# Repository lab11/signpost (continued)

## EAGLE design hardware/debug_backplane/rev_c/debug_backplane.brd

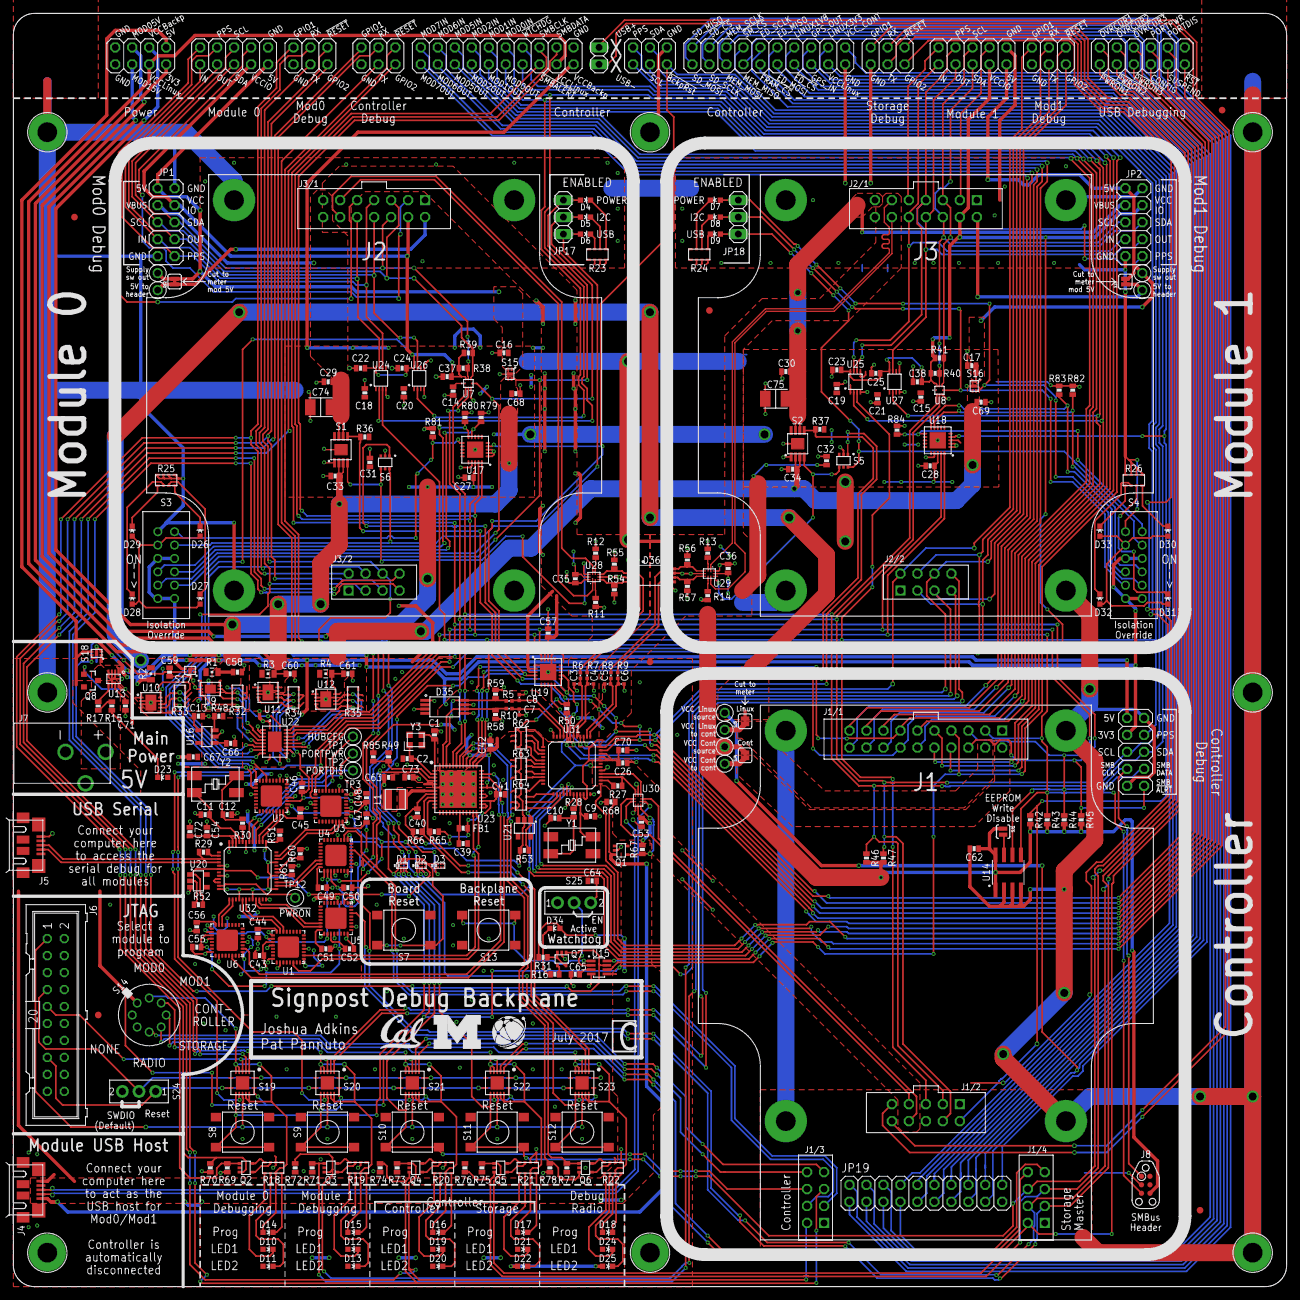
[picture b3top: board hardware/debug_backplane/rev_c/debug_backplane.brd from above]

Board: 2 copper layers, 190.5 x 190.5 mm, 327 parts (0 on the bottom side), 293 nets.

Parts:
C1, C2: 8pF; 0603_CAP
C3, C4, C5, C6, C7, C8: 22pF; 0402_CAP
C9, C10, C11, C12: 22pF; 0603_CAP
C13: 0.01uF; 0603_CAP
C14, C15, C16, C17, C18, C19, C20, C21, C22, C23, C24, C25, C26, C27, C28, C29, C30, C31, C32, C33, C34, C35, C36, C37, C38, C39, C40, C41, C42, C43, C44, C45, C46, C47, C48, C49, C50, C51, C52, C53, C54, C55, C56, C57, C58, C59, C60, C61, C62, C63: 0.1uF; 0603_CAP
C64: 0.47uF; 0603_CAP
C65: 0.82uF; 0603_CAP
C66, C67: 2.2uF; 0603_CAP
C68, C69, C70, C71, C72: 4.7uF; 0603_CAP
C73: 6.8uF; 0603_CAP
C74, C75: 150uF; 1210_CAP
D1, D2, D3: DIODE_SCHOTTKY_ARRAY-4HMD8; HMD8
D4, D5, D6, D7, D8, D9, D10, D11, D12, D13, D14, D15, D16, D17, D18, D19, D20, D21, D22, D23, D24, D25, D26, D27, D28, D29, D30, D31, D32, D33, D34: LED0603; LED-0603
D35, D36: SN75240-TSSOP; TSSOP-8
FB1: 1.5kR; 0603_CAP
H1, H2, H3, H4, H5, H6, H7, H8: MOUNT-PAD-ROUND#4; #4-PAD
J1: BACKPLANE_CONTROLLER_MODULE_DEBUG; BACKPLANE_MODULE_20PIN_10PIN_DEBUG
J2, J3: BACKPLANE_GENERIC_MODULE_DEBUG; BACKPLANE_MODULE_14PIN_8PIN
J4, J5: MICRO_USB_B_HIROSE_ZX62R-B-5P; USB_MICRO_B-HIROSE-ZX62R-B-5P
J6: ML20
J7: PJ-102AH
J8: TC2030-FTDI-I2C; TC2030-IDC-NL
JP1, JP2, JP4, JP5, JP11: 2X05
JP3, JP6, JP7, JP8, JP9, JP10, JP14: 2X03
JP12, JP19, JP20: 2X10
JP13: 1X02
JP15, JP21, JP22, JP23, JP24, JP25: FIDUCIAL1X2; FIDUCIAL-1X2
JP16: 2X04
JP17, JP18: 1X03
L1: 22uH; 1212
Q1, Q2, Q3, Q4, Q5, Q6, Q7: DMN32D2LDF; SOT353
Q8: MOSFET-NCHANNELSMD; SOT23-3
R1, R2, R3, R4: 0.017Ω; 0805_RES
R5, R6, R7, R8, R9, R10: 27Ω; 0402_RES-HIGH_SPEED
R11, R12, R13, R14, R15, R16, R17: 50Ω; 0603-RES
R18, R19, R20, R21, R22, R23, R24, R25, R26: 1kΩ; ARRAY-CONVEX-0603-4
R27, R28, R29, R30, R31: 1.5kΩ; 0603-RES
R32, R33, R34, R35: 1.8kΩ; ARRAY-CONVEX-0603-4
R36, R37, R38, R39, R40, R41, R42, R43, R44, R45, R46, R47, R48, R49, R50, R51, R52, R53: 10kΩ; 0603-RES
R54, R55, R56, R57, R58, R59, R60, R61: 15kΩ; 0603-RES
R62, R63, R64: 15kΩ; ARRAY-CONVEX-0603-4
R65, R66, R67, R68: 100kΩ; 0603-RES
R69, R70, R71, R72, R73, R74, R75, R76, R77, R78: 1MΩ; 0603-RES
R79, R80, R81, R82, R83, R84: 10MΩ; 0603-RES
R85: DNP; 0603-RES
S1, S2: AP2401MP; MSOP-8EP
S3, S4: MMS42
S5, S6: NC7SZ157; SC70-6
S7, S8, S9, S10, S11, S12, S13: PTS645SM43SMTR92; PTS645
S14: RM106772BCB; RM-SWITCH
S15, S16, S17, S18: SIP3240X; TDFN4
S19, S20, S21, S22, S23: SN74AHC4066-RGY; S-PVQFN-N14-3.5MM
S24, S25: TE_SSA12/SPDT
SJ1: SOLDERJUMPERNO; SJ_2S-NO
SJ2, SJ3, SJ4, SJ5: SOLDERJUMPERNC; SJ_2S
TP1, TP2, TP3, TP4, TP5, TP6, TP7, TP8, TP9, TP10, TP11, TP12: TEST_POINT_0.040IN; TESTPOINT_0.040IN
U1, U2, U3, U4, U5, U6: FT232RQ; QFN32
U7, U8: FXMA2102; UMLP-8
U9: LTC2941; DFN-6-2MMX3MM
U10, U11, U12: LTC2943; DFN-8
U13: LTC4360; SC70-8
U14: M24C01WMN; SOIC-8
U15: MAX6746; SOT-23-8
U16: MAX8887EZK33+T; SOT-23-5
U17, U18, U19: MCP23008QFN; QFN-20-4MM
U20, U21: NCP301LSN30; SOT23-5
U22: PCA9544AQFN-N20; QFN-N20
U23: SAM4LC8AA; QFN-48-7MM
U24, U25, U26, U27: SN74LVC2T45; VFSOP-8
U28, U29, U30: TS3USB30E; UQFN-10
U31, U32: TUSB2077A; LQFP-48
U$12: UMICH_SOLID_200MIL
U$15: UCB_CAL_200MIL
U$28: TERRASWARM_200MIL
Y1, Y2: ABMM
Y3: FH1600015; FHXXX

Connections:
3V3_UNMETERED: C40.1, C41.1, C42.1, C53.2, C54.2, C67.1, C72.2, D10.A, D11.A, D12.A, D13.A, D19.A, D20.A, D21.A, D22.A, D24.A, D25.A, D34.A, FB1.2, JP11.3, JP16.2, R31.2, R51.2, R52.2, R65.2, R66.2, R67.2, R85.2, S3.B1, S3.B2, S3.B3, S3.B4, S4.B1, S4.B2, S4.B3, S4.B4, S14.C, S17.3, S19.14, S20.14, S21.10, S21.14, S22.10, S22.14, S23.10, S23.14, U1.1, U6.1, U15.5, U15.8, U16.5, U20.2, U23.8, U23.27, U23.31, U23.40, U23.45, U30.9, U32.9, U32.10, U32.46, U32.47
3V3_WATCHDOGGED: R1.2, R32.A2, R32.B2, R32.C2, S17.1, U9.1
5V_UNMETERED: C43.1, C46.1, C48.1, C50.1, C52.1, C55.1, C66.1, C71.1, D23.A, JP11.1, JP16.1, Q8.2, R48.2, S18.3, U1.19, U2.19, U3.19, U4.19, U5.19, U6.19, U13.7, U16.1
5V_WATCHDOGGED: R2.2, R3.2, R4.2, R33.A2, R33.B2, R33.C2, R34.A2, R34.B2, R34.C2, R35.A2, R35.B2, R35.C2, S18.1, U10.P1, U11.P1, U12.P1
!BACKPLANE_RESET: D3.1A, J1.22, JP14.2, R42.1, U17.4, U18.4, U19.4
!POWER_ON_RESET: D2.4A, R52.1, U20.1, U32.6
!SMBALERT: J1.6, JP11.10, JP12.6, R45.1, U22.17
!WATCHDOG: J1.7, JP12.7, U15.6
CONT0_!RESET: D1.3A, J1.105, JP9.1, S10.3, S10.4, S21.9
CONT0_DBG_GPIO1: J1.101, JP9.5, Q4.G1, R73.2
CONT0_DBG_GPIO2: J1.104, JP9.2, Q4.G2, R74.2
CONT0_DBG_RX: J1.103, JP9.3, U4.30
CONT0_DBG_TX: J1.102, JP9.4, U4.2
CONT0_SWDCLK: J1.106, S21.3
CONT0_SWDIO: J1.107, S21.2
CONT0_VCCIO: C49.1, U4.16
CONT1_!RESET: D1.4A, J1.205, JP10.1, S11.3, S11.4, S22.9
CONT1_DBG_GPIO1: J1.201, JP10.5, Q5.G1, R75.2
CONT1_DBG_GPIO2: J1.204, JP10.2, Q5.G2, R76.2
CONT1_DBG_RX: J1.203, JP10.3, U5.30
CONT1_DBG_TX: J1.202, JP10.4, U5.2
CONT1_SWDCLK: J1.206, S22.3
CONT1_SWDIO: J1.207, S22.2
CONT1_VCCIO: C51.1, U5.16
CONTROLLER_BUCK/LDO_N: R49.2, R85.1, U23.3
CONT_DBG_PIN1: JP19.1, JP20.1
CONT_DBG_PIN2: JP19.2, JP20.2
CONT_DBG_PIN3: JP19.3, JP20.3
CONT_DBG_PIN4: JP19.4, JP20.4
CONT_DBG_PIN5: JP19.5, JP20.5
CONT_DBG_PIN6: JP19.6, JP20.6
CONT_DBG_PIN7: JP19.7, JP20.7
CONT_DBG_PIN8: JP19.8, JP20.8
CONT_DBG_PIN9: JP19.9, JP20.9
CONT_DBG_PIN10: JP19.10, JP20.10
CONT_DBG_PIN11: JP19.11, JP20.11
CONT_DBG_PIN12: JP19.12, JP20.12
CONT_DBG_PIN13: JP19.13, JP20.13
CONT_DBG_PIN14: JP19.14, JP20.14
CONT_DBG_PIN15: JP19.15, JP20.15
CONT_DBG_PIN16: JP19.16, JP20.16
CONT_DBG_PIN18: JP19.18, JP20.18
CONT_DBG_PIN20: JP19.20, JP20.20
CONT_MOD0_IN: J1.9, JP12.9, U24.2
CONT_MOD0_OUT: J1.10, JP12.10, U26.2
CONT_MOD1_IN: J1.11, JP12.11, U25.2
CONT_MOD1_OUT: J1.12, JP12.12, U27.2
CONT_MOD2_IN: J1.13, JP12.13, U23.39
CONT_MOD2_OUT: J1.14, JP12.14, U23.38
CONT_MOD5_IN: J1.15, JP12.15
CONT_MOD5_OUT: J1.16, JP12.16
CONT_MOD6_IN: J1.17, JP12.17
CONT_MOD6_OUT: J1.18, JP12.18
CONT_MOD7_IN: J1.19, JP12.19
CONT_MOD7_OUT: J1.20, JP12.20
CONT_USB+: J1.27, U30.6
CONT_USB-: J1.28, U30.2
DBG_USB_!PWRON: TP12.TESTPOINT, U32.11
DBG_USB_DM0: J5.2, U32.4
DBG_USB_DM1: U6.15, U32.13
DBG_USB_DM2: U1.15, U32.17
DBG_USB_DM3: U5.15, U32.21
DBG_USB_DM4: U4.15, U32.26
DBG_USB_DM5: R61.1, U32.30
DBG_USB_DM6: U3.15, U32.34
DBG_USB_DM7: U2.15, U32.38
DBG_USB_DP0: J5.3, R29.1, U32.3
DBG_USB_DP1: U6.14, U32.14
DBG_USB_DP2: U1.14, U32.18
DBG_USB_DP3: U5.14, U32.22
DBG_USB_DP4: U4.14, U32.27
DBG_USB_DP5: R60.1, U32.31
DBG_USB_DP6: U3.14, U32.35
DBG_USB_DP7: U2.14, U32.39
DBG_USB_HUBCFG: TP1.TESTPOINT, U32.40
DBG_USB_PORTDIS: TP3.TESTPOINT, U32.42
DBG_USB_PORTPWR: TP2.TESTPOINT, U32.41
DBG_USB_XTAL1: C11.2, U32.45, Y2.3
DBG_USB_XTAL2: R30.2, U32.44
DEBUG_HUB_!OVRCURX: R51.1, U32.12, U32.16, U32.20, U32.25, U32.29, U32.33, U32.37
FAKE_RADIO_XIN: C1.1, U23.1, Y3.3
FAKE_RADIO_XOUT: C2.1, U23.2, Y3.1
FTDI_!RESET: D2.3A, U1.18, U2.18, U3.18, U4.18, U5.18, U6.18
GND: C1.2, C2.2, C3.2, C4.2, C5.2, C6.2, C7.2, C8.2, C9.1, C10.1, C11.1, C12.1, C13.2, C14.2, C15.2, C16.2, C17.2, C18.2, C19.2, C20.2, C21.2, C22.2, C23.2, C24.2, C25.2, C26.1, C27.2, C28.2, C29.2, C30.2, C31.2, C32.2, C33.2, C34.2, C35.1, C36.1, C37.2, C38.2, C39.2, C40.2, C41.2, C42.2, C43.2, C44.2, C45.2, C46.2, C47.2, C48.2, C49.2, C50.2, C51.2, C52.2, C53.1, C54.1, C55.2, C56.2, C57.2, C58.2, C59.2, C60.2, C61.2, C62.2, C63.2, C64.2, C65.2, C66.2, C67.2, C68.2, C69.2, C70.1, C71.2, C72.1, C73.2, C74.2, C75.2, D35.1, D35.3, D35.5, D35.7, D36.1, D36.3, D36.5, D36.7, H1.B#4, H2.B#4, H3.B#4, H4.B#4, H5.B#4, H6.B#4, H7.B#4, H8.B#4, J1.1, J1.21, J1.100, J1.200, J1.MNT1, J1.MNT2, J1.MNT3, J1.MNT4, J2.1, J2.14, J2.15, J2.MNT1, J2.MNT2, J2.MNT3, J2.MNT4, J3.1, J3.14, J3.15, J3.MNT1, J3.MNT2, J3.MNT3, J3.MNT4, J4.5, J5.5, J6.4, J6.6, J6.8, J6.10, J6.12, J6.14, J6.16, J6.18, J6.20, J7.2, J8.3, JP1.2, JP1.9, JP2.2, JP2.9, JP3.6, JP4.1, JP5.1, JP6.6, JP9.6, JP10.6, JP11.2, JP11.9, JP12.1, JP14.1, JP16.7, JP16.8, JP19.19, JP20.19, Q1.S, Q2.S, Q3.S, Q4.S, Q5.S, Q6.S, Q7.S, R11.2, R12.2, R13.2, R14.2, R18.C1, R18.D1, R19.C1, R19.D1, R20.C1, R20.D1, R21.C1, R21.D1, R22.C1, R22.D1, R23.A1, R23.B1, R23.C1, R24.A1, R24.B1, R24.C1, R25.A2, R25.B2, R25.C2, R25.D2, R26.A2, R26.B2, R26.C2, R26.D2, R49.1, R54.1, R55.1, R56.1, R57.1, R58.1, R59.1, R60.2, R61.2, R62.B2, R62.C2, R63.A2, R63.B2, R63.D2, R64.A2, R64.C2, R64.D2, R68.1, R69.1, R70.1, R71.1, R72.1, R73.1, R74.1, R75.1, R76.1, R77.1, R78.1, R79.1, R80.1, R81.1, R82.1, R83.1, R84.1, S1.1, S1.PAD, S2.1, S2.PAD, S3.A1, S4.A1, S5.2, S6.2, S7.3, S7.4, S8.1, S8.2, S9.1, S9.2, S10.1, S10.2, S11.1, S11.2, S12.1, S12.2, S13.1, S13.2, S15.2, S15.PAD, S16.2, S16.PAD, S17.2, S17.PAD, S18.2, S18.PAD, S19.7, S20.7, S21.7, S22.7, S23.7, S25.1, U1.4, U1.17, U1.20, U1.24, U1.26, U2.4, U2.17, U2.20, U2.24, U2.26, U3.4, U3.17, U3.20, U3.24, U3.26, U4.4, U4.17, U4.20, U4.24, U4.26, U5.4, U5.17, U5.20, U5.24, U5.26, U6.4, U6.17, U6.20, U6.24, U6.26, U7.4, U8.4, U9.2, U10.P2, U10.P3, U10.P7, U10.P$1, U11.P2, U11.P3, U11.P7, U11.P$1, U12.P2, U12.P3, U12.P7, U12.P$1, U13.2, U13.3, U13.4, U13.6, U14.2, U14.3, U14.4, U15.4, U16.2, U17.1, U17.2, U17.3, U17.17, U17.GND, U18.1, U18.2, U18.17, U18.GND, U19.1, U19.17, U19.GND, U20.3, U21.3, U22.1, U22.2, U22.3, U22.10, U23.6, U23.17, U23.30, U23.48, U23.THERMAL, U24.4, U25.4, U26.4, U26.5, U27.4, U27.5, U28.4, U28.10, U29.4, U29.10, U30.4, U30.8, U31.5, U31.24, U31.43, U31.48, U32.5, U32.8, U32.24, U32.43, U32.48, Y3.2, Y3.4
HUB_!OVRCUR1: JP8.2, R37.1, S2.5, U31.12
HUB_!OVRCUR2: JP8.4, R36.1, S1.5, U31.16
HUB_!OVRCUR3: JP8.6, R50.1, U31.20
HUB_!OVRCUR4: R62.A1, U31.25
HUB_!OVRCUR5: R62.D1, U31.29
HUB_!OVRCUR6: R63.C1, U31.33
HUB_!OVRCUR7: R64.B1, U31.37
HUB_!PWRON1: JP8.1, S5.1, U19.10, U31.11
HUB_!PWRON2: JP8.3, S6.1, U19.11, U31.15
HUB_!PWRON3: JP8.5, U19.12, U31.19
HUB_CFG: JP7.1, U31.40
HUB_DM1: C6.1, R9.2, U31.13
HUB_DM2: C4.1, R7.2, U31.17
HUB_DM3: C8.1, R5.2, U31.21
HUB_DM4: R62.B1, U31.26
HUB_DM5: R63.A1, U31.30
HUB_DM6: R63.D1, U31.34
HUB_DM7: R64.C1, U31.38
HUB_DP1: C5.1, R8.2, U31.14
HUB_DP2: C3.1, R6.2, U31.18
HUB_DP3: C7.1, R10.2, U31.22
HUB_DP4: R62.C1, U31.27
HUB_DP5: R63.B1, U31.31
HUB_DP6: R64.A1, U31.35
HUB_DP7: R64.D1, U31.39
HUB_PORTDIS: JP7.4, U31.42
HUB_PORTPWR: JP7.2, U31.41
JTAG_!RESET: J6.15, S19.8, S20.8, S21.8, S22.8, S23.8, S24.1
JTAG_SWDCLK: J6.9, S19.4, S20.4, S21.4, S22.4, S23.4
JTAG_SWDIO: J6.7, S19.1, S20.1, S21.1, S22.1, S23.1, S24.IN
JTAG_VTREF: J6.1, S19.11, S20.11, S21.11, S22.11, S23.11
MASTER_!RESET: D1.1K, D1.2K, D1.3K, D1.4K, D2.1K, D2.2K, D2.3K, D2.4K, D3.1K, S7.1, S7.2
MOD0_5V: C16.1, JP1.1, JP4.2, S15.1, SJ2.2, TP5.TESTPOINT
MOD0_5V_HEADER: J2.2, SJ2.1, TP4.TESTPOINT
MOD0_5V_METERED: C33.1, C60.1, C68.1, JP16.5, R3.1, S1.2, S1.3, S15.3, U11.P8
MOD0_D+_HUB-SW: D36.4, R6.1, R54.2, U28.3
MOD0_D-_HUB-SW: D36.2, R7.1, R55.2, U28.5
MOD0_DBG_!RESET: D1.1A, J2.20, JP3.1, S8.3, S8.4, S19.9
MOD0_DBG_GPIO1: J2.16, JP3.5, Q2.G1, R69.2
MOD0_DBG_GPIO2: J2.19, JP3.2, Q2.G2, R70.2
MOD0_DBG_RX: J2.18, JP3.3, U2.30
MOD0_DBG_SWDCLK: J2.21, S19.3
MOD0_DBG_SWDIO: J2.22, S19.2
MOD0_DBG_TX: J2.17, JP3.4, U2.2
MOD0_IN: J2.10, JP1.7, JP4.10, U24.7
MOD0_ISO_I2C: D5.A, JP17.2, S3.COM3, U7.5
MOD0_ISO_OVERRIDE: D26.A, D27.A, D28.A, D29.A, S3.COM1
MOD0_ISO_P0: R79.2, S3.A4, U17.9
MOD0_ISO_P1: R80.2, S3.A3, U17.10
MOD0_ISO_P2: R81.2, S3.A2, U17.11
MOD0_ISO_POWER: D4.A, JP17.3, S3.COM4, S15.4
MOD0_ISO_USB: D6.A, JP17.1, S3.COM2, S6.6
MOD0_OUT: J2.8, JP1.8, JP4.8, U26.7
MOD0_PPS: J2.7, JP1.10, JP4.7, U24.6
MOD0_SCL: J2.5, JP1.5, JP4.5, R39.2, U7.6
MOD0_SDA: J2.6, JP1.6, JP4.6, R38.2, U7.7
MOD0_USB+: J2.11, U28.1
MOD0_USB-: J2.12, U28.7
MOD0_USB_!EN: S1.4, S6.4, U28.8
MOD0_USB_VBUS: C29.1, C74.1, J2.13, JP1.3, S1.6, S1.7
MOD0_VCCIO: C22.1, C24.1, C37.1, J2.4, JP1.4, JP4.4, R38.1, R39.1, S19.10, U2.1, U7.8, U24.8, U26.8
MOD1_5V: C17.1, JP2.1, JP5.2, S16.1, SJ3.2, TP7.TESTPOINT
MOD1_5V_HEADER: J3.2, SJ3.1, TP6.TESTPOINT
MOD1_5V_METERED: C34.1, C61.1, C69.1, JP16.6, R4.1, S2.2, S2.3, S16.3, U12.P8
MOD1_D+_HUB-SW: D36.8, R8.1, R56.2, U29.3
MOD1_D-_HUB-SW: D36.6, R9.1, R57.2, U29.5
MOD1_DBG_!RESET: D1.2A, J3.20, JP6.1, S9.3, S9.4, S20.9
MOD1_DBG_GPIO1: J3.16, JP6.5, Q3.G1, R71.2
MOD1_DBG_GPIO2: J3.19, JP6.2, Q3.G2, R72.2
MOD1_DBG_RX: J3.18, JP6.3, U3.30
MOD1_DBG_SWDCLK: J3.21, S20.3
MOD1_DBG_SWDIO: J3.22, S20.2
MOD1_DBG_TX: J3.17, JP6.4, U3.2
MOD1_IN: J3.10, JP2.7, JP5.10, U25.7
MOD1_ISO_I2C: D8.A, JP18.2, S4.COM3, U8.5
MOD1_ISO_OVERRIDE: D30.A, D31.A, D32.A, D33.A, S4.COM1
MOD1_ISO_P0: R82.2, S4.A4, U18.9
MOD1_ISO_P1: R83.2, S4.A3, U18.10
MOD1_ISO_P2: R84.2, S4.A2, U18.11
MOD1_ISO_POWER: D7.A, JP18.3, S4.COM4, S16.4
MOD1_ISO_USB: D9.A, JP18.1, S4.COM2, S5.6
MOD1_OUT: J3.8, JP2.8, JP5.8, U27.7
MOD1_PPS: J3.7, JP2.10, JP5.7, U25.6
MOD1_SCL: J3.5, JP2.5, JP5.5, R41.2, U8.6
MOD1_SDA: J3.6, JP2.6, JP5.6, R40.2, U8.7
MOD1_USB+: J3.11, U29.1
MOD1_USB-: J3.12, U29.7
MOD1_USB_!EN: S2.4, S5.4, U29.8
MOD1_USB_VBUS: C30.1, C75.1, J3.13, JP2.3, S2.6, S2.7
MOD1_VCCIO: C23.1, C25.1, C38.1, J3.4, JP2.4, JP5.4, R40.1, R41.1, S20.10, U3.1, U8.8, U25.8, U27.8
MOD2_DBG_GPIO1: Q6.G1, R77.2, U23.41
MOD2_DBG_GPIO2: Q6.G2, R78.2, U23.42
MOD2_USB+: D35.6, R10.1, R58.2, U23.47
MOD2_USB-: D35.8, R5.1, R59.2, U23.46
MOD_SCL: J1.24, JP11.5, JP14.4, R47.1, U7.3, U8.3, U23.44
MOD_SDA: J1.23, JP11.6, JP14.3, R46.1, U7.2, U8.2, U23.43
MOD_USB_OVERRIDE_5V: J4.1, Q1.G2, R68.2
MOD_USB_OVERRIDE_DM: J4.2, U30.1
MOD_USB_OVERRIDE_DP: J4.3, U30.7
unnamed: D4.C, R23.A2
unnamed: D5.C, R23.B2
unnamed: D6.C, R23.C2
unnamed: R48.1, U16.3
unnamed: D10.C, R18.A2
unnamed: D11.C, R18.B2
unnamed: C13.1, U16.4
unnamed: Q2.D1, R18.A1
unnamed: Q2.D2, R18.B1
unnamed: D7.C, R24.C2
unnamed: D9.C, R24.A2
unnamed: R27.2, U31.2
unnamed: D8.C, R24.B2
unnamed: C10.2, R28.1, Y1.1
unnamed: D12.C, R19.A2
unnamed: D13.C, R19.B2
unnamed: R11.1, U28.2
unnamed: Q3.D1, R19.A1
unnamed: Q3.D2, R19.B1
unnamed: Q4.D1, R20.A1
unnamed: C56.1, U6.16
unnamed: Q4.D2, R20.B1
unnamed: D21.C, R21.A2
unnamed: D22.C, R21.B2
unnamed: R14.1, U29.6
unnamed: R13.1, U29.2
unnamed: D14.C, R18.D2
unnamed: Q5.D1, R21.A1
unnamed: Q5.D2, R21.B1
unnamed: R12.1, U28.6
unnamed: D15.C, R19.D2
unnamed: Q1.D2, R67.1, U30.10
unnamed: C45.1, U2.16
unnamed: D16.C, R20.D2
unnamed: D17.C, R21.D2
unnamed: C39.1, FB1.1, U23.19
unnamed: U23.28, U23.29
unnamed: U23.25, U23.26
unnamed: D18.C, R22.D2
unnamed: R32.B1, U9.4, U22.5
unnamed: SJ1.2, U14.7
unnamed: D24.C, R22.A2
unnamed: R32.A1, U9.3, U22.6
unnamed: D25.C, R22.B2
unnamed: C44.1, U1.16
unnamed: C47.1, U3.16
unnamed: R34.B1, U11.P5, U22.12
unnamed: R34.A1, U11.P4, U22.13
unnamed: R34.C1, U11.P6, U22.11
unnamed: R35.B1, U12.P5, U22.15
unnamed: R35.A1, U12.P4, U22.16
unnamed: R35.C1, U12.P6, U22.14
unnamed: Q6.D1, R22.A1
unnamed: Q6.D2, R22.B1
unnamed: D29.C, R25.D1
unnamed: D28.C, R25.C1
unnamed: D27.C, R25.B1
unnamed: D26.C, R25.A1
unnamed: C65.1, U15.3
unnamed: D30.C, R26.A1
unnamed: R32.C1, U9.5, U22.4
unnamed: R33.B1, U10.P5, U22.8
unnamed: D19.C, R20.A2
unnamed: R33.A1, U10.P4, U22.9
unnamed: R33.C1, U10.P6, U22.7
unnamed: D20.C, R20.B2
unnamed: C9.2, U31.45, Y1.3
unnamed: R28.2, U31.44
unnamed: D31.C, R26.B1
unnamed: D32.C, R26.C1
unnamed: D33.C, R26.D1
unnamed: Q7.D1, Q7.G2, R31.1
unnamed: S13.3, S13.4, U15.1
unnamed: D34.C, R16.2
unnamed: Q7.D2, R16.1
unnamed: R17.1, U13.5
unnamed: R15.1, R17.2
unnamed: D23.C, R15.2
unnamed: R29.2, U32.2
unnamed: C12.2, R30.1, Y2.1
OVERVOLT_PROT_CTL: Q8.1, U13.8
PPS: J1.25, JP11.4, JP14.5, U23.37, U24.3, U25.3
PROG0_EN: D14.A, R18.C2, S14.1, S19.5, S19.6, S19.12, S19.13
PROG1_EN: D15.A, R19.C2, S14.2, S20.5, S20.6, S20.12, S20.13
PROG2_EN: D16.A, R20.C2, S14.3, S21.5, S21.6, S21.12, S21.13
PROG3_EN: D17.A, R21.C2, S14.4, S22.5, S22.6, S22.12, S22.13
PROG4_EN: D18.A, R22.C2, S14.5, S23.5, S23.6, S23.12, S23.13
RADIO_!RESET: D2.1A, S12.3, S12.4, S23.9, U23.4
RADIO_DEBUG_RX: U6.30, U23.34
RADIO_DEBUG_TX: U6.2, U23.35
RADIO_SWDCLK: R66.1, S23.3, U23.9
RADIO_SWDIO: R65.1, S23.2, U23.10
RADIO_UPLINK_RX: U1.30, U23.23
RADIO_UPLINK_TX: U1.2, U23.24
RADIO_VDDCORE: C63.1, C73.1, L1.P$2, U23.5
RADIO_VDDOUT: L1.P$1, U23.7
SMBCLK: J1.5, J8.1, JP11.7, JP12.5, R44.1, U14.6, U17.19, U18.19, U19.19, U22.18
SMBDATA: J1.3, J8.5, JP11.8, JP12.3, R43.1, U14.5, U17.20, U18.20, U19.20, U22.19
USB+: R27.1, U30.5, U31.3
USB-: U30.3, U31.4
USB_!RESET: D2.2A, JP7.5, R53.1, U19.9, U21.1, U31.6
USB_SUSPEND_STATUS: JP7.3, U31.1
VCC_BACKPLANE: C14.1, C15.1, C18.1, C19.1, C20.1, C21.1, C26.2, C27.1, C28.1, C31.1, C32.1, C35.2, C36.2, C57.1, C58.1, C62.1, C70.2, J8.6, JP12.2, JP16.3, R1.1, R36.2, R37.2, R42.2, R43.2, R44.2, R45.2, R46.2, R47.2, R50.2, R53.2, R62.A2, R62.D2, R63.C2, R64.B2, S5.3, S5.5, S6.3, S6.5, SJ1.1, SJ4.2, TP9.TESTPOINT, U4.1, U5.1, U7.1, U8.1, U9.6, U14.1, U14.8, U17.18, U18.3, U18.18, U19.2, U19.3, U19.18, U21.2, U22.20, U24.1, U24.5, U25.1, U25.5, U26.1, U27.1, U28.9, U29.9, U31.8, U31.9, U31.10, U31.46, U31.47
VCC_BARRELJACK: J7.1, Q8.3, U13.1
VCC_CONTROLLER_HEADER: J1.2, SJ4.1, TP8.TESTPOINT
VCC_LINUX: C59.1, JP12.4, JP16.4, JP19.17, JP20.17, R2.1, SJ5.2, TP11.TESTPOINT, U10.P8
VCC_LINUX_HEADER: J1.4, SJ5.1, TP10.TESTPOINT
WATCHDOG_!RESET: Q7.G1, S17.4, S18.4, U15.7
WDT_CTRL: S25.IN, U15.2
WDT_ON: C64.1, S25.2

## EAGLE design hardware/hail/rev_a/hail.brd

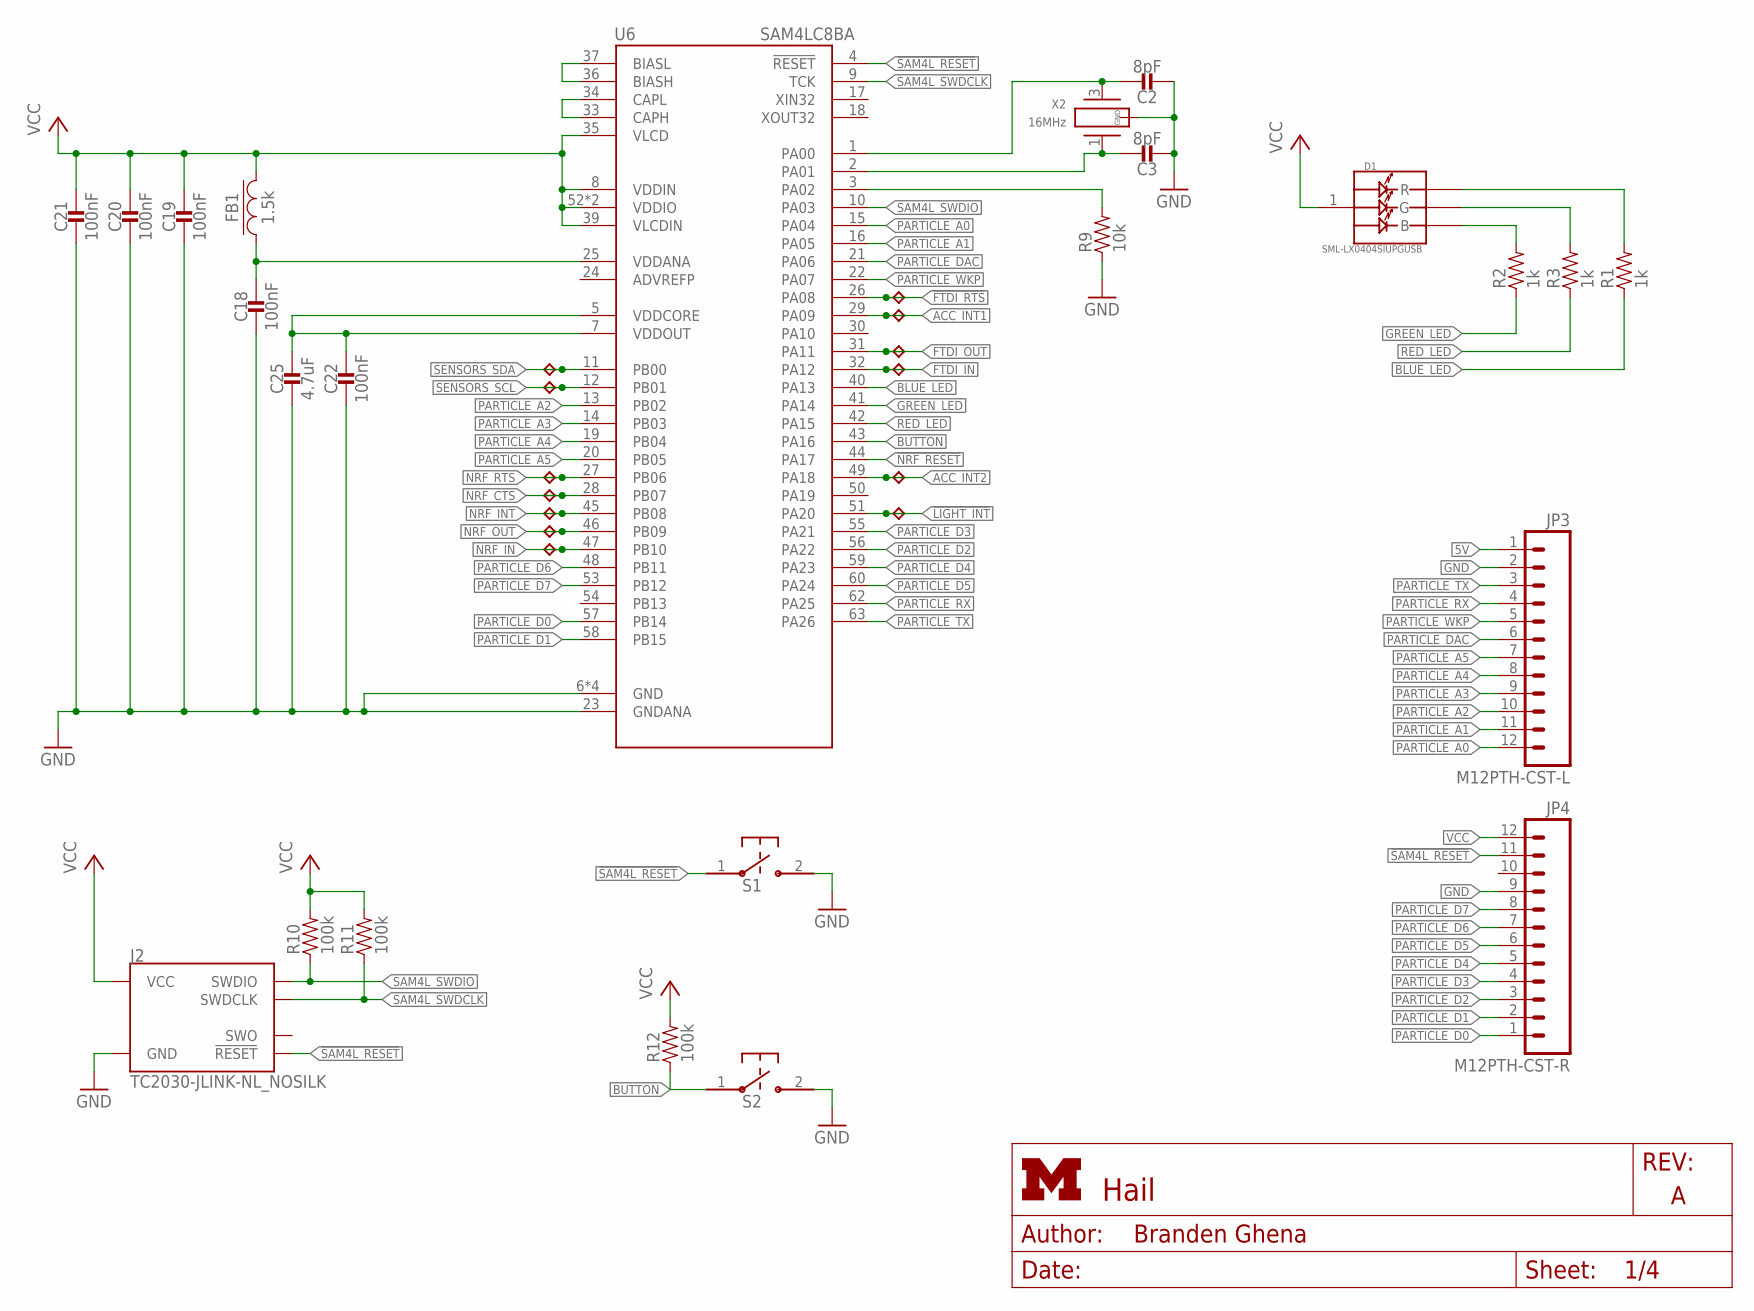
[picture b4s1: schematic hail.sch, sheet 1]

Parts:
C2, C3: 8pF; 0402_CAP; DIGIKEY 490-8230-1-ND
C18, C19, C20, C21, C22: 100nF; 0402_CAP; DIGIKEY 490-10777-1-ND
C25: 4.7uF; 0402_CAP; DIGIKEY 490-13252-1-ND
D1: SML-LX0404SIUPGUSB; 1MM_SQ_4PAD
FB1: 1.5k; 0402_CAP; DIGIKEY 490-5216-1-ND
J2: TC2030-JLINK-NL_NOSILK; TC2030-IDC-NL_NOSILK
JP3: M12PTH-CST-L; 1X12-CASTELLATED
JP4: M12PTH-CST-R; 1X12-CASTELLATED
R1, R2, R3: 1k; 0402_RES; DIGIKEY 1276-3430-1-ND
R9: 10k; 0402_RES; DIGIKEY 1276-3431-1-ND
R10, R11, R12: 100k; 0402_RES; DIGIKEY 1276-3432-1-ND
S1, S2: B3U-1000P
TP1, TP2, TP3, TP4, TP5, TP6, TP7, TP8, TP9, TP10, TP11, TP12, TP13: TPB1,27; B1,27
U6: SAM4LC8BA; QFN-64-9MM; DIGIKEY ATSAM4LC8BA-MURCT-ND
X2: 16MHz; FHXXX

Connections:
5V: JP3.1 (12); also elsewhere on the board
!FTDI_RTS: TP11.TP, U6.26 (PA08); also elsewhere on the board
!LIGHT_INT: TP10.TP, U6.51 (PA20); also elsewhere on the board
!NRF_RESET: U6.44 (PA17); also elsewhere on the board
!SAM4L_RESET: J2.3 (!RESET), JP4.11, S1.1, U6.4 (!RESET); also elsewhere on the board
ACC_INT1: TP8.TP, U6.29 (PA09); also elsewhere on the board
ACC_INT2: TP9.TP, U6.49 (PA18); also elsewhere on the board
ADVREFP: U6.24 (ADVREFP)
BLUE_LED: R1.1, U6.40 (PA13)
BUCK/LDO_N1: R9.2, U6.3 (PA02)
BUTTON: R12.1, S2.1, U6.43 (PA16)
FTDI_IN: TP13.TP, U6.32 (PA12); also elsewhere on the board
FTDI_OUT: TP12.TP, U6.31 (PA11); also elsewhere on the board
GND: C2.2, C3.2, C18.2, C19.2, C20.2, C21.2, C22.2, C25.2, J2.5 (GND), JP3.2 (11), JP4.9, R9.1, S1.2, S2.2, U6.6 (GND), U6.23 (GNDANA), U6.38 (GND), U6.64 (GND), U6.GND, X2.2 (GND), X2.4 (GND); also elsewhere on the board
GREEN_LED: R2.1, U6.41 (PA14)
unnamed: D1.3 (B), R2.2
unnamed: D1.4 (G), R3.2
unnamed: D1.2 (R), R1.2
unnamed: U6.36 (BIASH), U6.37 (BIASL)
unnamed: U6.33 (CAPH), U6.34 (CAPL)
unnamed: C18.1, FB1.1, U6.25 (VDDANA)
unnamed: C22.1, C25.1, U6.5 (VDDCORE), U6.7 (VDDOUT)
NRF_CTS: TP2.TP, U6.28 (PB07); also elsewhere on the board
NRF_IN: TP5.TP, U6.47 (PB10); also elsewhere on the board
NRF_INT: TP3.TP, U6.45 (PB08); also elsewhere on the board
NRF_OUT: TP4.TP, U6.46 (PB09); also elsewhere on the board
NRF_RTS: TP1.TP, U6.27 (PB06); also elsewhere on the board
PARTICLE_A0: JP3.12 (1), U6.15 (PA04)
PARTICLE_A1: JP3.11 (2), U6.16 (PA05)
PARTICLE_A2: JP3.10 (3), U6.13 (PB02)
PARTICLE_A3: JP3.9 (4), U6.14 (PB03)
PARTICLE_A4: JP3.8 (5), U6.19 (PB04)
PARTICLE_A5: JP3.7 (6), U6.20 (PB05)
PARTICLE_D0: JP4.1, U6.57 (PB14)
PARTICLE_D1: JP4.2, U6.58 (PB15)
PARTICLE_D2: JP4.3, U6.56 (PA22)
PARTICLE_D3: JP4.4, U6.55 (PA21)
PARTICLE_D4: JP4.5, U6.59 (PA23)
PARTICLE_D5: JP4.6, U6.60 (PA24)
PARTICLE_D6: JP4.7, U6.48 (PB11)
PARTICLE_D7: JP4.8, U6.53 (PB12)
PARTICLE_DAC: JP3.6 (7), U6.21 (PA06)
PARTICLE_RX: JP3.4 (9), U6.62 (PA25)
PARTICLE_TX: JP3.3 (10), U6.63 (PA26)
PARTICLE_WKP: JP3.5 (8), U6.22 (PA07)
RED_LED: R3.1, U6.42 (PA15)
SAM4L_SWDCLK: J2.4 (SWDCLK), R11.1, U6.9 (TCK)
SAM4L_SWDIO: J2.2 (SWDIO), R10.1, U6.10 (PA03)
SAM4L_XIN1: C2.1, U6.1 (PA00), X2.3 (2)
SAM4L_XOUT1: C3.1, U6.2 (PA01), X2.1
SENSORS_SCL: TP7.TP, U6.12 (PB01); also elsewhere on the board
SENSORS_SDA: TP6.TP, U6.11 (PB00); also elsewhere on the board
VCC: C19.1, C20.1, C21.1, D1.1 (VDD), FB1.2, J2.1 (VCC), JP4.12, R10.2, R11.2, R12.2, U6.8 (VDDIN), U6.35 (VLCD), U6.39 (VLCDIN), U6.52 (VDDIO), U6.61 (VDDIO); also elsewhere on the board

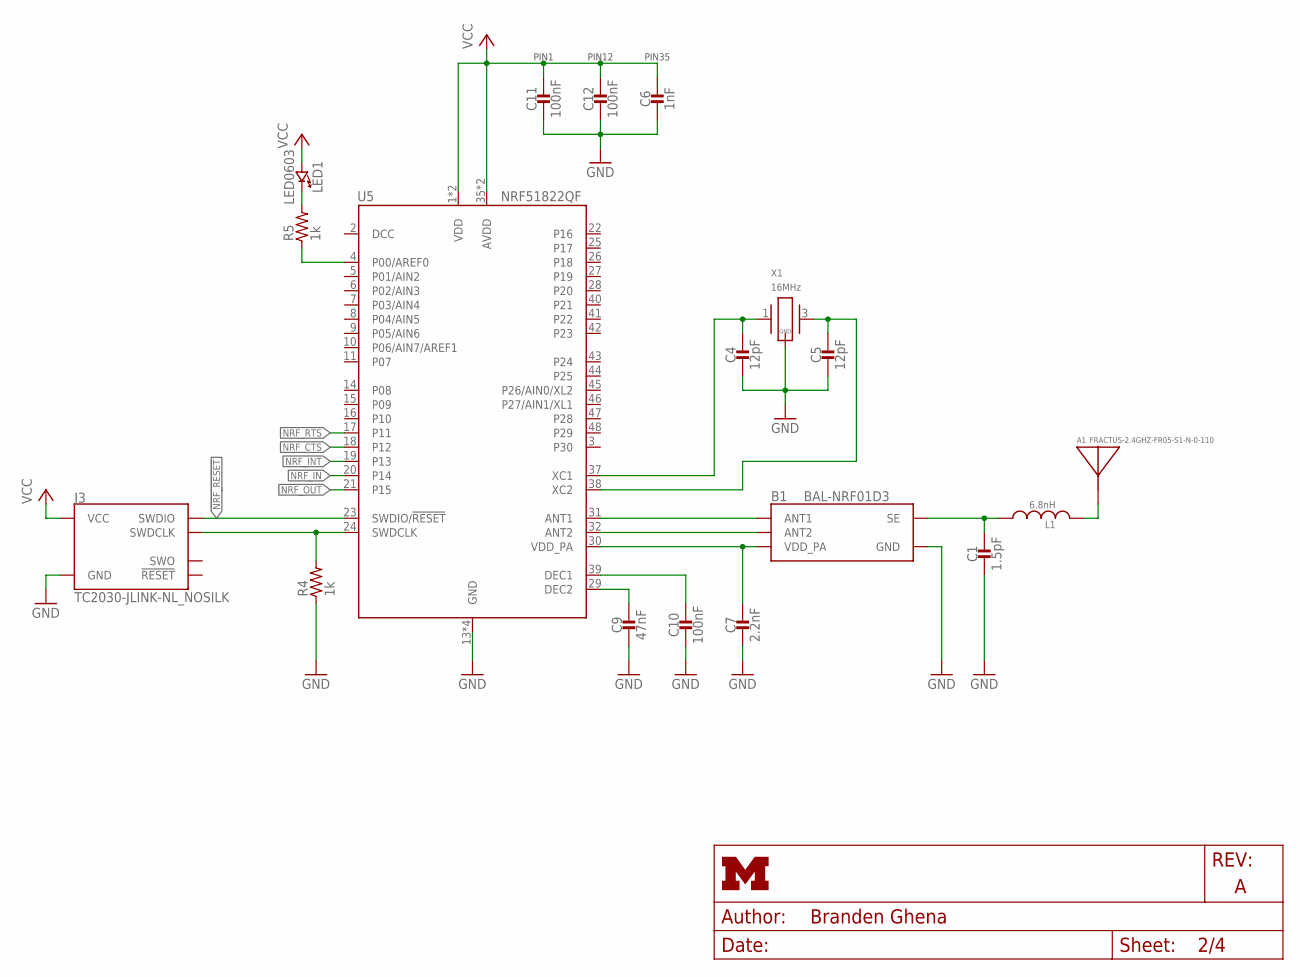
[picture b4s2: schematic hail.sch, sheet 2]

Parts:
A1: FRACTUS-2.4GHZ-FR05-S1-N-0-110; FRACTUS-ANTENNA-FR05-S1-N-0-110
B1: BAL-NRF01D3
C1: 1.5pF; 0402_CAP; DIGIKEY 490-6212-1-ND
C4, C5: 12pF; 0402_CAP; DIGIKEY 490-6197-1-ND
C6: 1nF; 0402_CAP; DIGIKEY 490-1303-1-ND
C7: 2.2nF; 0402_CAP; DIGIKEY 490-5419-1-ND
C9: 47nF; 0402_CAP; DIGIKEY 445-1264-1-ND
C10, C11, C12: 100nF; 0402_CAP; DIGIKEY 490-10777-1-ND
J3: TC2030-JLINK-NL_NOSILK; TC2030-IDC-NL_NOSILK
L1: 6.8nH; 0402_CAP; DIGIKEY 490-6840-1-ND
LED1: LED0603; LED-0603; DIGIKEY 160-1837-6-ND
R4, R5: 1k; 0402_RES; DIGIKEY 1276-3430-1-ND
U5: NRF51822QF; QFN-48-6MM; DIGIKEY 1490-1049-1-ND
X1: 16MHz; TXC-8Y; DIGIKEY 887-2003-1-ND

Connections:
!NRF_RESET: J3.2 (SWDIO), U5.23 (SWDIO/!RESET); also elsewhere on the board
GND: B1.GND, C1.2, C4.2, C5.2, C6.2, C7.2, C9.2, C10.2, C11.2, C12.2, J3.5 (GND), R4.1, U5.13 (GND), U5.33 (GND), U5.34 (GND), U5.GND, X1.2 (GND), X1.4 (GND); also elsewhere on the board
unnamed: C10.1, U5.39 (DEC1)
unnamed: C9.1, U5.29 (DEC2)
unnamed: J3.4 (SWDCLK), R4.2, U5.24 (SWDCLK)
unnamed: R5.1, U5.4 (P00/AREF0)
unnamed: LED1.C (CATHODE), R5.2
unnamed: B1.ANT1, U5.31 (ANT1)
unnamed: B1.VCC (VDD_PA), C7.1, U5.30 (VDD_PA)
unnamed: B1.ANT2, U5.32 (ANT2)
unnamed: C4.1, U5.37 (XC1), X1.1
unnamed: C5.1, U5.38 (XC2), X1.3 (2)
unnamed: B1.SE, C1.1, L1.1
unnamed: A1.ANT, L1.2
NRF_CTS: U5.18 (P12); also elsewhere on the board
NRF_IN: U5.20 (P14); also elsewhere on the board
NRF_INT: U5.19 (P13); also elsewhere on the board
NRF_OUT: U5.21 (P15); also elsewhere on the board
NRF_RTS: U5.17 (P11); also elsewhere on the board
VCC: C6.1, C11.1, C12.1, J3.1 (VCC), LED1.A (ANODE), U5.1 (VDD), U5.12 (VDD), U5.35 (AVDD), U5.36 (AVDD); also elsewhere on the board

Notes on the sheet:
PIN35
PIN1
PIN12

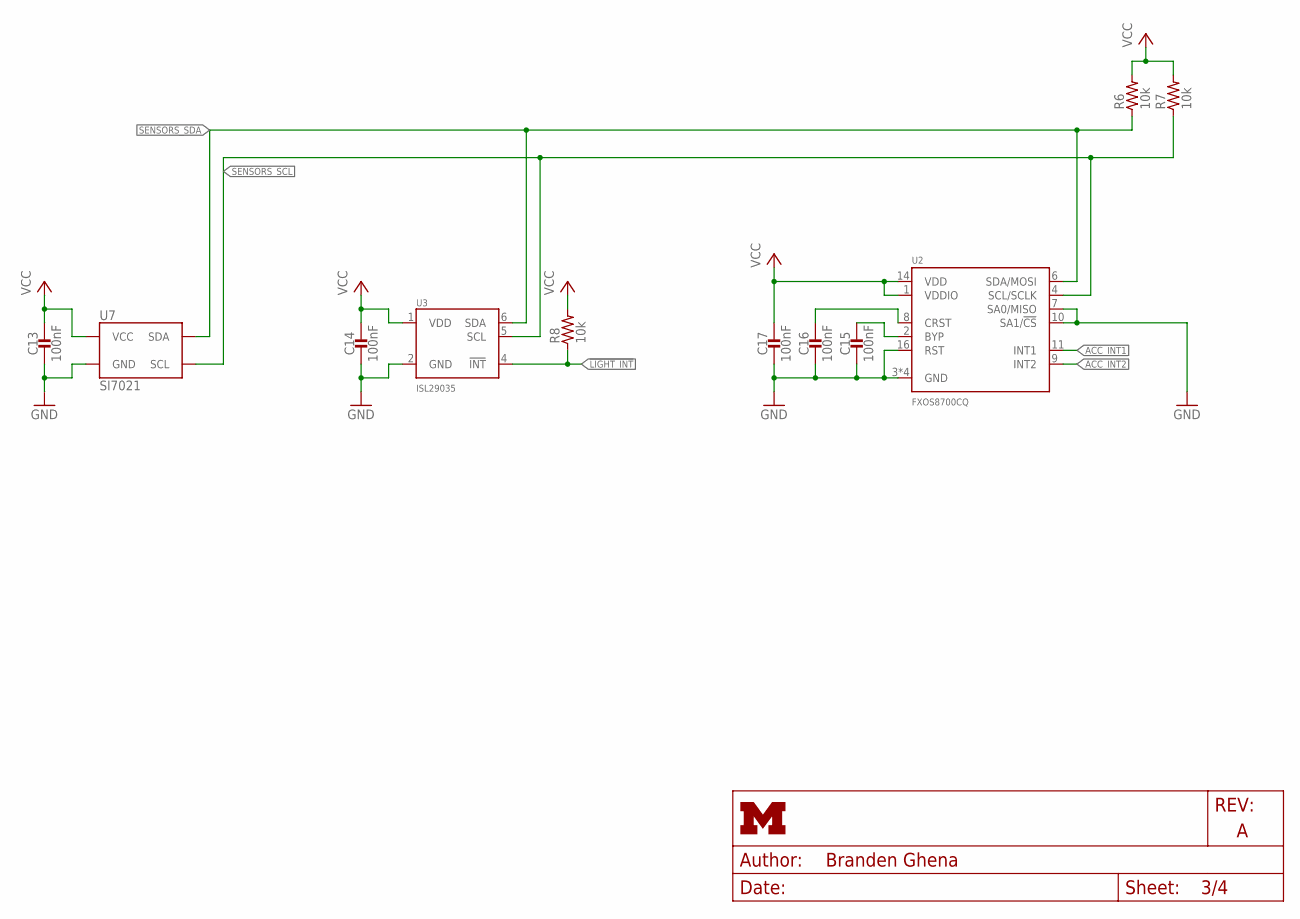
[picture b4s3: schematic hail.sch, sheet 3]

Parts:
C13, C14, C15, C16, C17: 100nF; 0402_CAP; DIGIKEY 490-10777-1-ND
R6, R7, R8: 10k; 0402_RES; DIGIKEY 1276-3431-1-ND
U2: FXOS8700CQ; QFN-16-3MM
U3: ISL29035; ODFN-6-1.5MMX1.6MM
U7: SI7021; DFN-6/3MM; DIGIKEY 336-3141-ND

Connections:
!LIGHT_INT: R8.1, U3.4 (!INT); also elsewhere on the board
ACC_INT1: U2.11 (INT1); also elsewhere on the board
ACC_INT2: U2.9 (INT2); also elsewhere on the board
GND: C13.2, C14.2, C15.2, C16.2, C17.2, U2.3 (GND), U2.5 (GND), U2.7 (SA0/MISO), U2.10 (SA1/!CS), U2.12 (GND), U2.13 (GND), U2.16 (RST), U3.2 (GND), U7.2 (GND); also elsewhere on the board
unnamed: C15.1, U2.2 (BYP)
unnamed: C16.1, U2.8 (CRST)
SENSORS_SCL: R7.1, U2.4 (SCL/SCLK), U3.5 (SCL), U7.6 (SCL); also elsewhere on the board
SENSORS_SDA: R6.1, U2.6 (SDA/MOSI), U3.6 (SDA), U7.1 (SDA); also elsewhere on the board
VCC: C13.1, C14.1, C17.1, R6.2, R7.2, R8.2, U2.1 (VDDIO), U2.14 (VDD), U3.1 (VDD), U7.5 (VCC); also elsewhere on the board

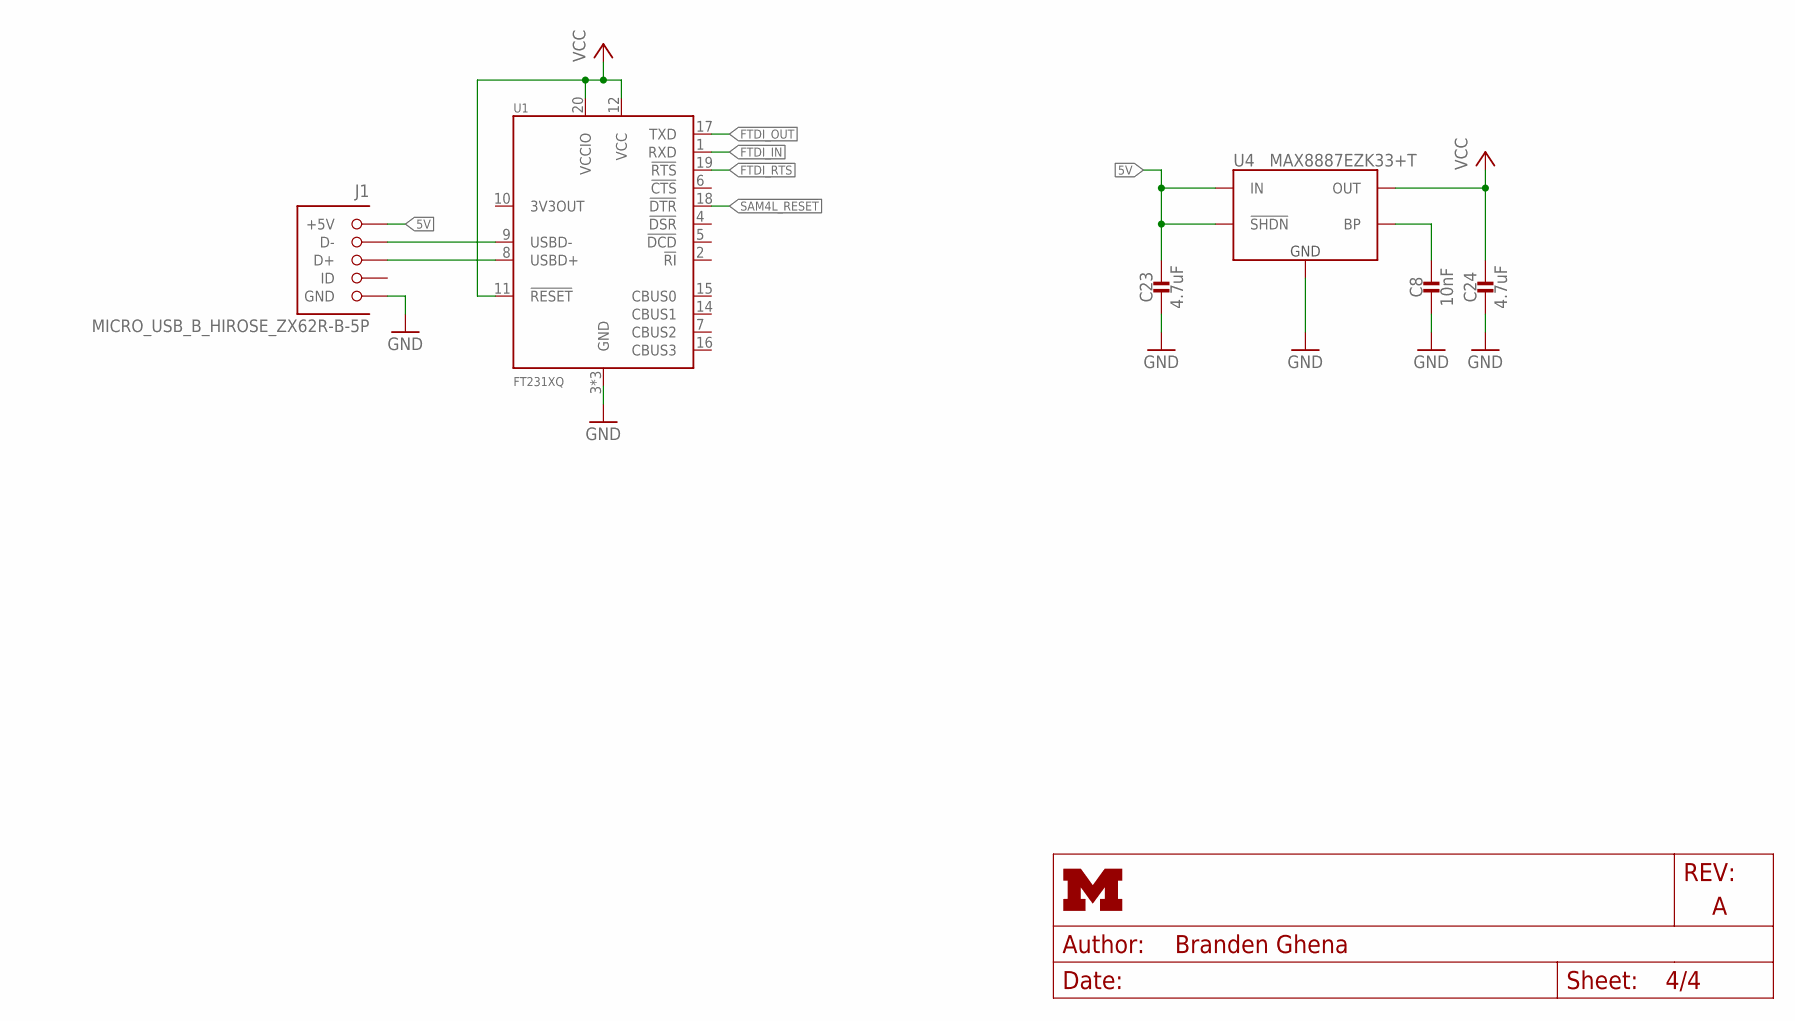
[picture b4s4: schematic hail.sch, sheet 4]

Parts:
C8: 10nF; 0402_CAP; DIGIKEY 490-7763-1-ND
C23, C24: 4.7uF; 0402_CAP; DIGIKEY 490-13252-1-ND
J1: MICRO_USB_B_HIROSE_ZX62R-B-5P; USB_MICRO_B-HIROSE-ZX62R-B-5P; DIGIKEY H125274CT-ND
U1: FT231XQ; QFN-20-4MM
U4: MAX8887EZK33+T; SOT-23-5

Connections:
5V: C23.1, J1.1 (+5V), U4.1 (IN), U4.3 (!SHDN); also elsewhere on the board
!FTDI_RTS: U1.19 (!RTS); also elsewhere on the board
!SAM4L_RESET: U1.18 (!DTR); also elsewhere on the board
FTDI_IN: U1.1 (RXD); also elsewhere on the board
FTDI_OUT: U1.17 (TXD); also elsewhere on the board
GND: C8.2, C23.2, C24.2, J1.5 (GND), U1.3 (GND), U1.13 (GND), U1.GND, U4.2 (GND); also elsewhere on the board
unnamed: J1.2 (D-), U1.9 (USBD-)
unnamed: J1.3 (D+), U1.8 (USBD+)
unnamed: C8.1, U4.4 (BP)
VCC: C24.1, U1.11 (!RESET), U1.12 (VCC), U1.20 (VCCIO), U4.5 (OUT); also elsewhere on the board

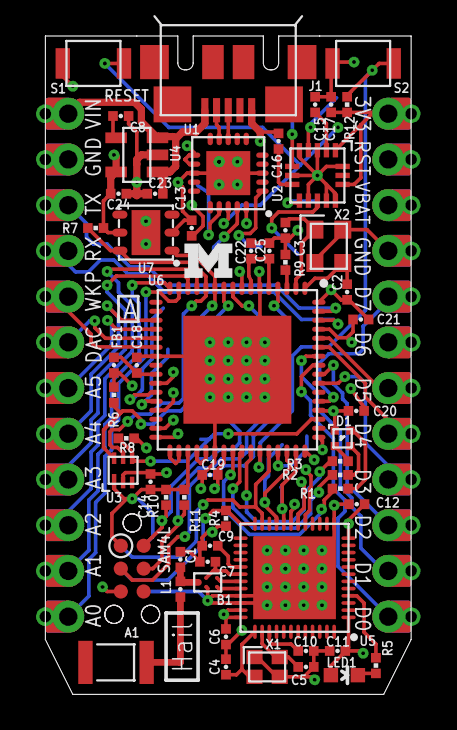
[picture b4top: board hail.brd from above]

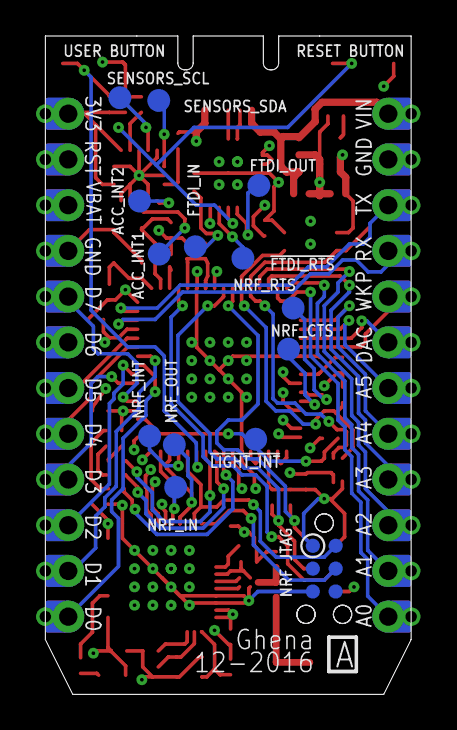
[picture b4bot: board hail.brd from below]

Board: 4 copper layers, 20.3 x 36.6 mm, 75 parts (14 on the bottom side), 69 nets.

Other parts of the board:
U$1: PHOTON-BOTTOM-SS
U$2: PHOTON-TOP-SS
U$3: UMICH_SOLID_75MIL
